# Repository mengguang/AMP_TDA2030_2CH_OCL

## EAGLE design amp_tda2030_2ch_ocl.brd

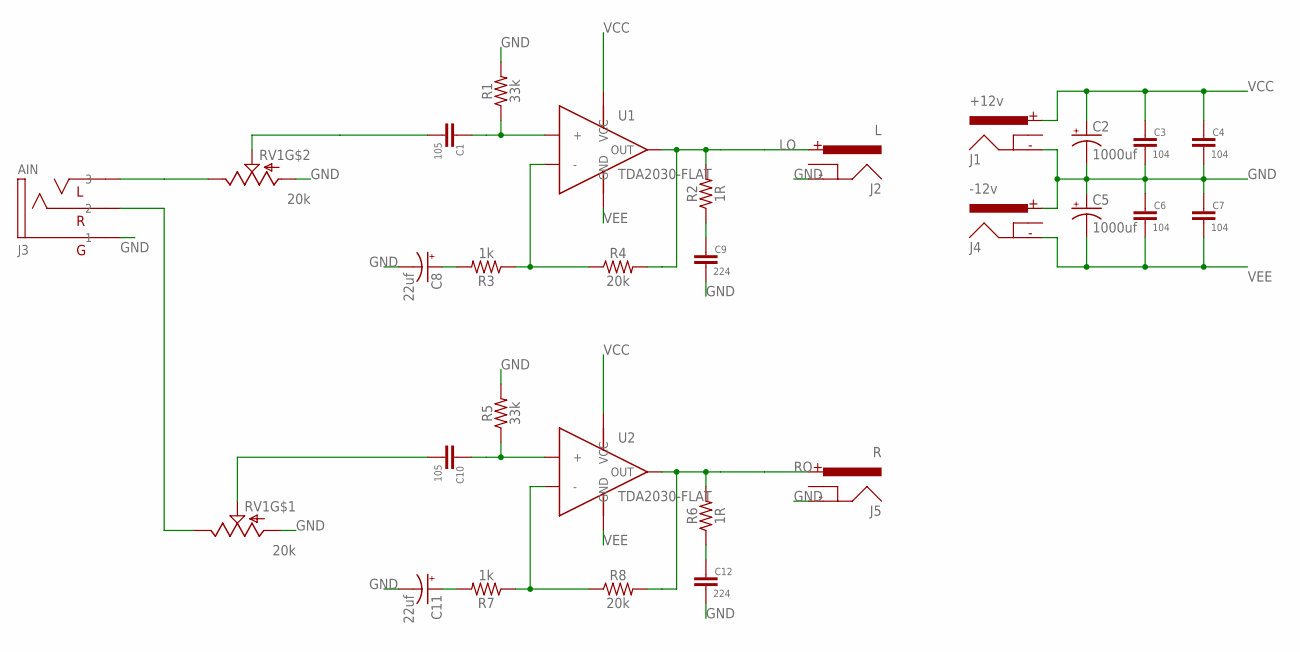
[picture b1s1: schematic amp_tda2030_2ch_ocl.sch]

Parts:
C1, C10: 105; CAP_5MM
C2, C5: 1000uf; CAP_5MM_10D
C3, C4, C6, C7: 104; C0603
C8, C11: 22uf; CAP_2.5MM
C9, C12: 224; C0603
J1: +12v; POWER_JACK_PTH_LOCK
J2: L; POWER_JACK_PTH_LOCK
J3: AIN; 3.5MM
J4: -12v; POWER_JACK_PTH_LOCK
J5: R; POWER_JACK_PTH_LOCK
R1, R5: 33k; R0603
R2, R6: 1R; R0603
R3, R7: 1k; R0603
R4, R8: 20k; R0603
RV1: 20k; POT_DUAL_GREEN
U1, U2: TDA2030-FLAT; TO220-FLAT

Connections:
GND: C2.-, C3.2, C4.2, C5.+, C6.1, C7.1, C8.-, C9.2, C11.-, C12.2, J1.GND, J2.GND, J3.P$1 (1), J4.PWR, J5.GND, R1.2, R5.2, RV1.P$1 (A), RV1.P$4 (A)
LO: J2.PWR, R2.2, R4.2, U1.4 (OUT)
unnamed: C1.P$1 (1), R1.1, U1.1 (+)
unnamed: C1.P$2 (2), RV1.P$5 (S)
unnamed: C10.P$2 (2), RV1.P$2 (S)
unnamed: C8.+, R3.2
unnamed: R3.1, R4.1, U1.2 (-)
unnamed: J3.P$3 (3), RV1.P$6 (E)
unnamed: J3.P$2 (2), RV1.P$3 (E)
unnamed: C10.P$1 (1), R5.1, U2.1 (+)
unnamed: C9.1, R2.1
unnamed: C11.+, R7.2
unnamed: R7.1, R8.1, U2.2 (-)
unnamed: C12.1, R6.1
RO: J5.PWR, R6.2, R8.2, U2.4 (OUT)
VCC: C2.+, C3.1, C4.1, J1.PWR, U1.5 (VCC), U2.5 (VCC)
VEE: C5.-, C6.2, C7.2, J4.GND, U1.3 (GND), U1.TAB (GND), U2.3 (GND), U2.TAB (GND)

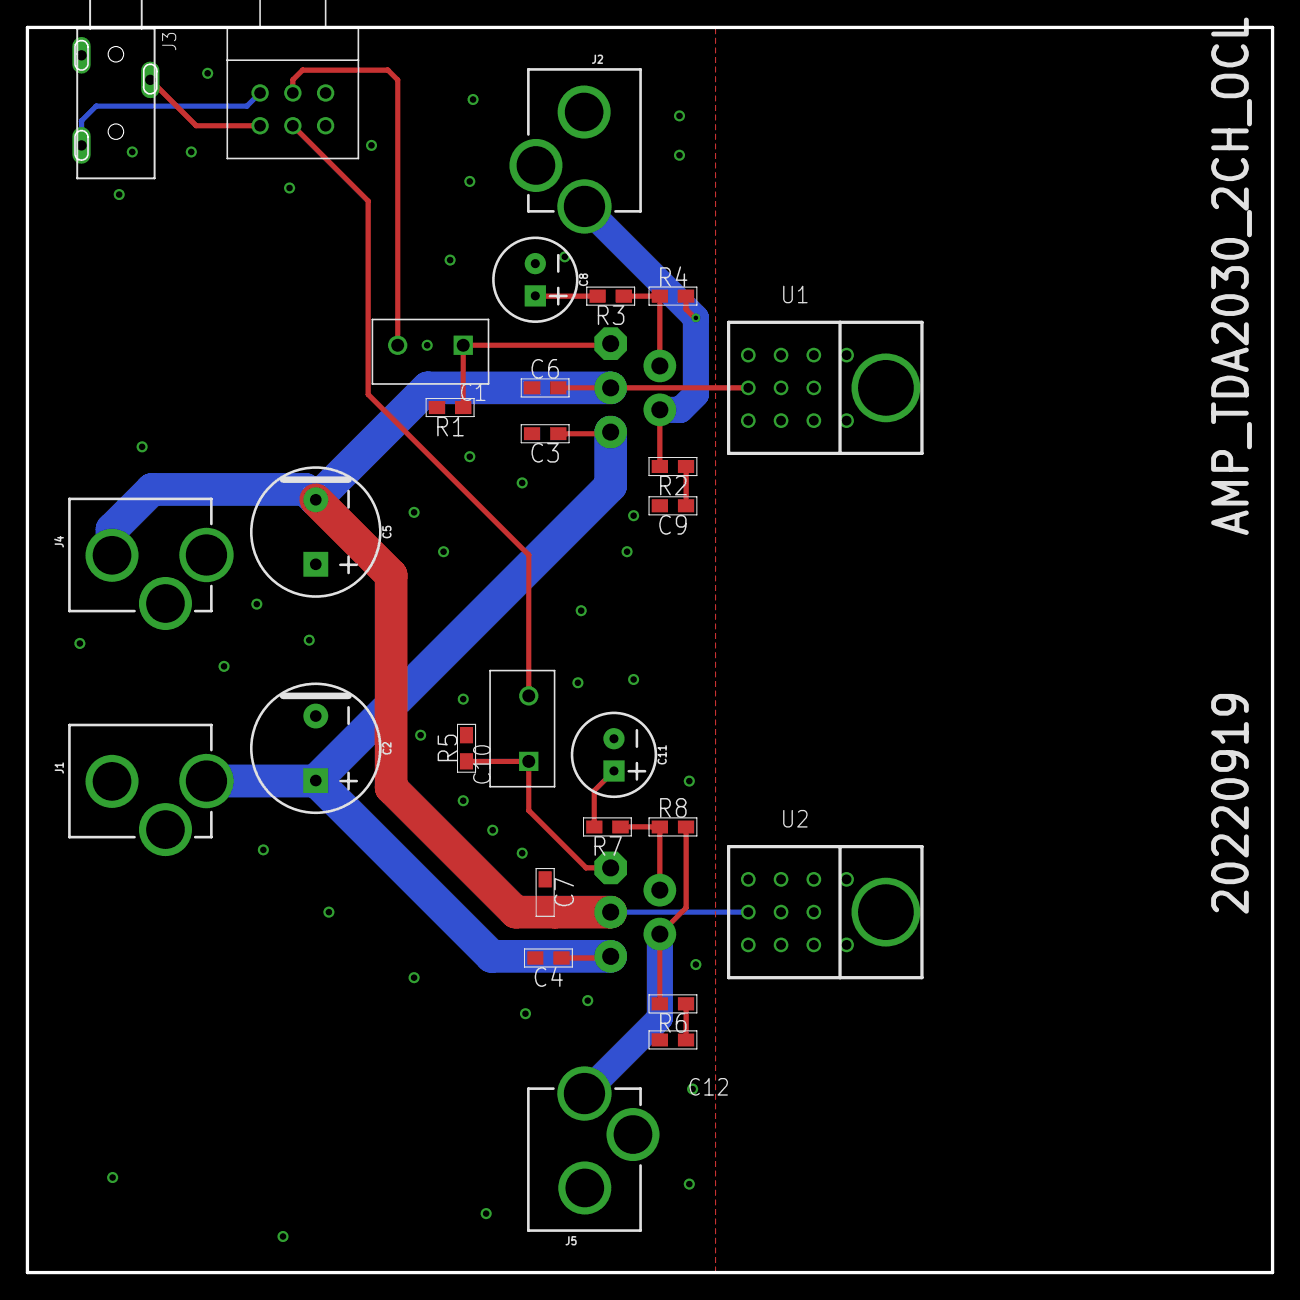
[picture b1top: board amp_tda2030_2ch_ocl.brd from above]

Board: 2 copper layers, 96.5 x 96.5 mm, 28 parts (0 on the bottom side), 17 nets.

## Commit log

2022-09-29 20220919
